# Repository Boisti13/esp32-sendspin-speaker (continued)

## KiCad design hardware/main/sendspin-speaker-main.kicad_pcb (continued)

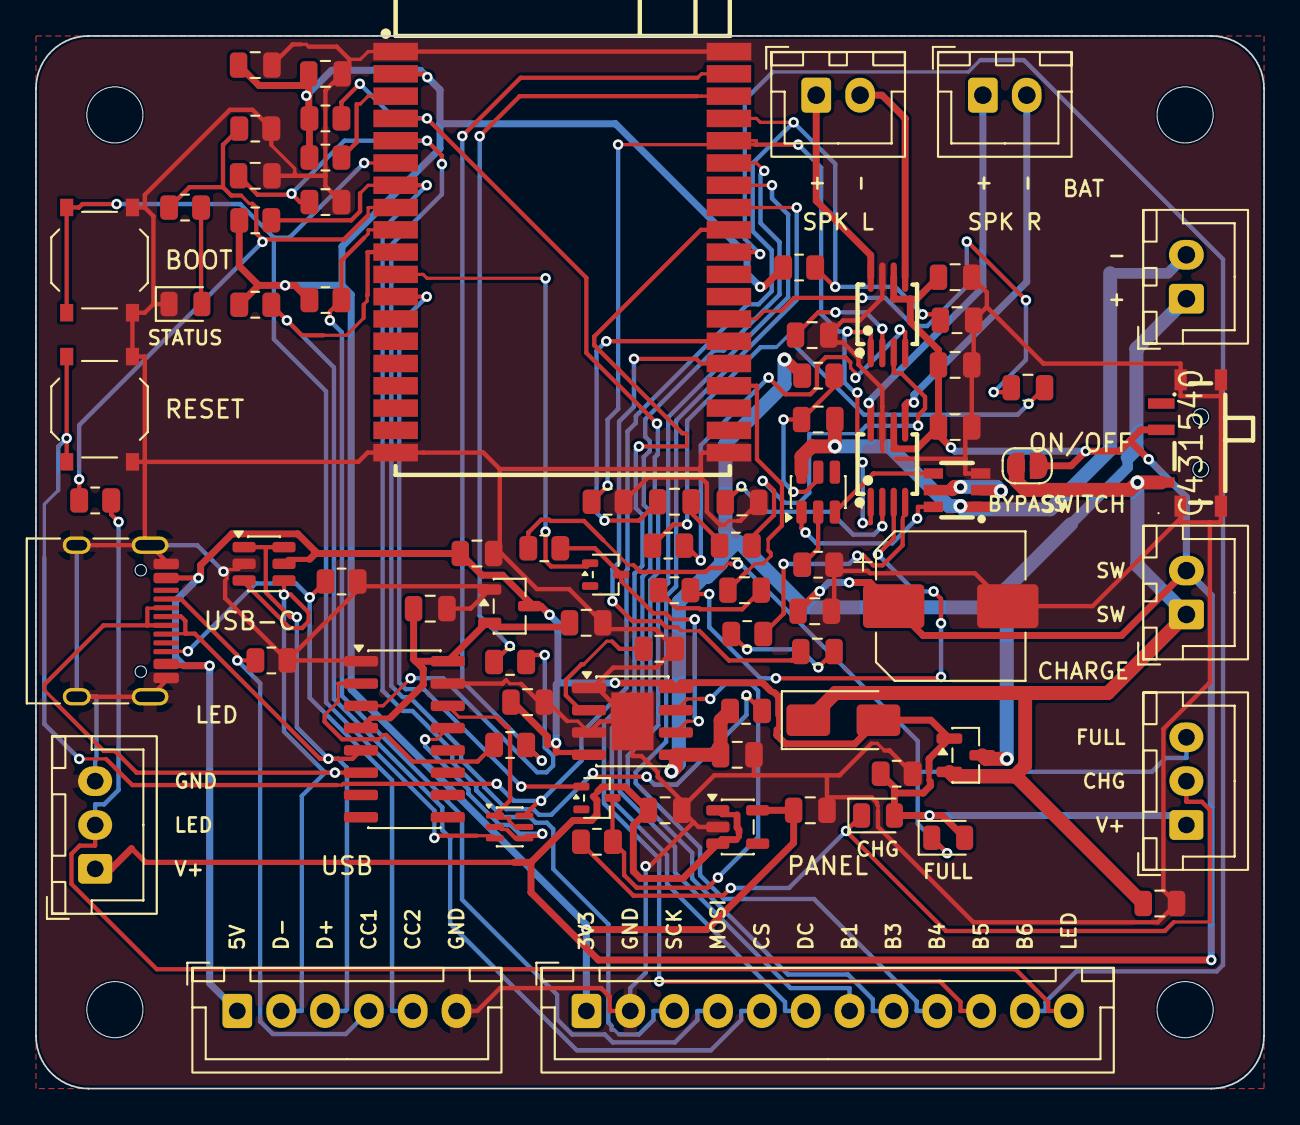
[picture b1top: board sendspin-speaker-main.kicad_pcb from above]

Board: 2 copper layers, 70.0 x 60.0 mm, 85 parts (0 on the bottom side), 65 nets.

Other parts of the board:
H1, H2, H3, H4: MountingHole_3.2mm_M3

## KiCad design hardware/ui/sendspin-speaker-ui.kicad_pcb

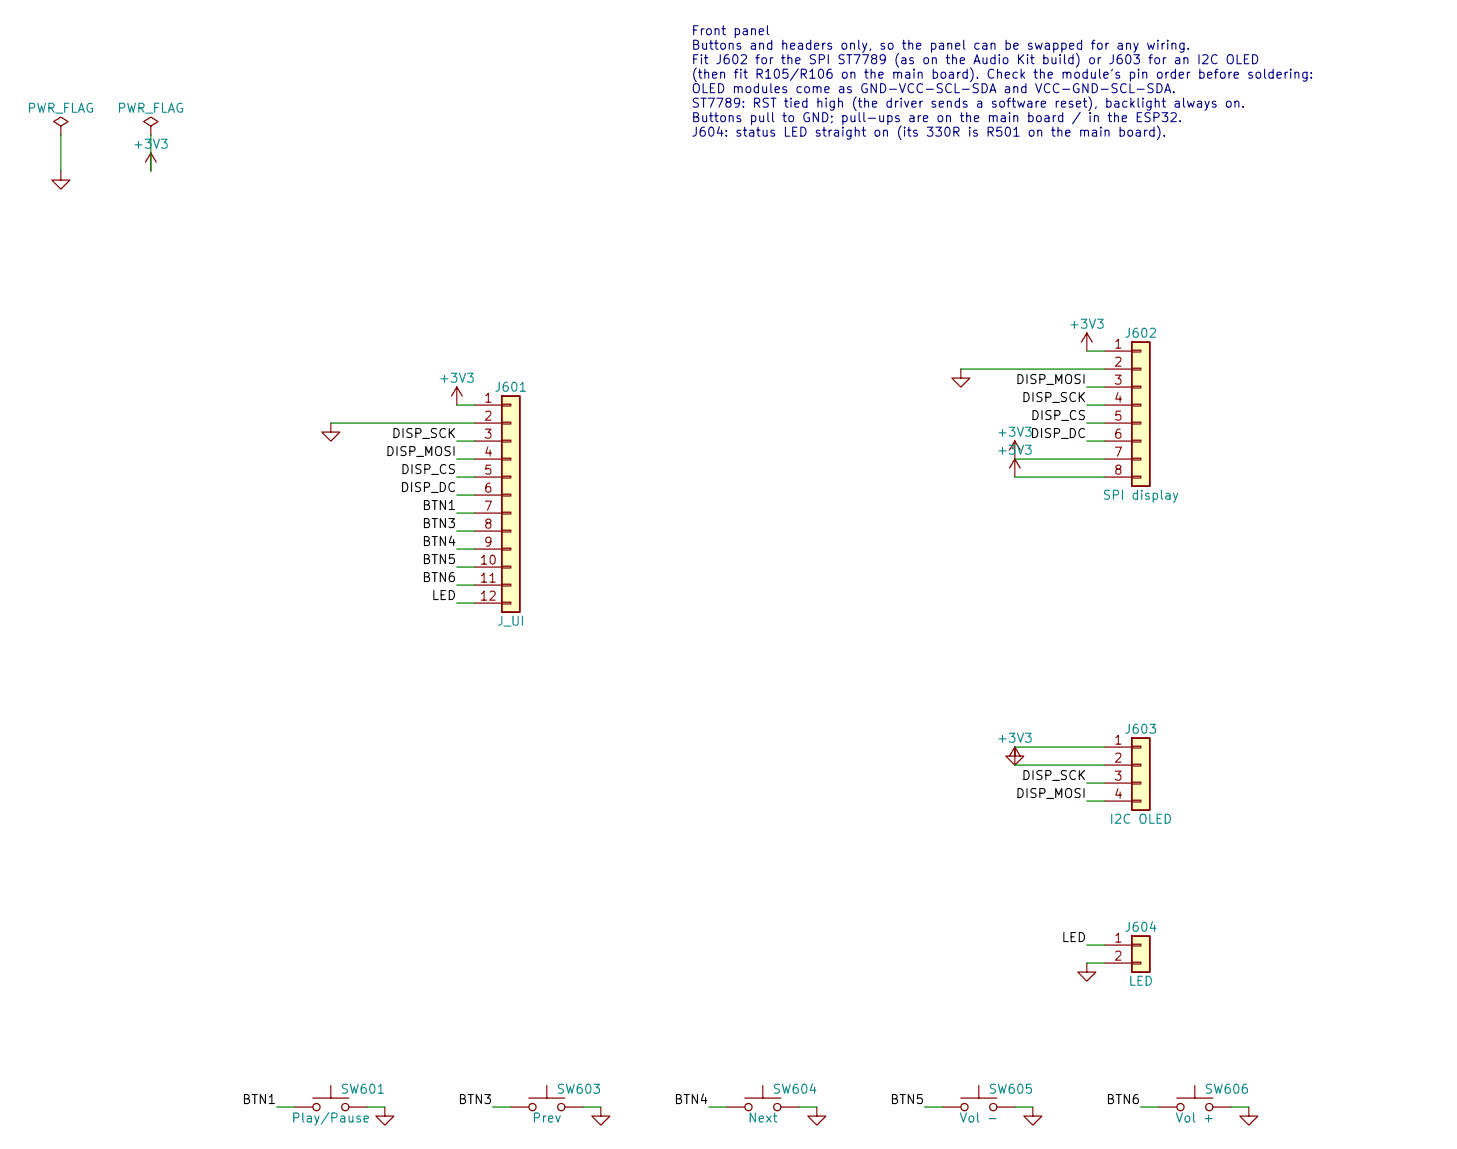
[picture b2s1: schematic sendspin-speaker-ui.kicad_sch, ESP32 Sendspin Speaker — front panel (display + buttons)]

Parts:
J601: J_UI; JST_XH_B12B-XH-A_1x12_P2.50mm_Vertical
J602: SPI display; PinHeader_1x08_P2.54mm_Vertical
J603: I2C OLED; PinHeader_1x04_P2.54mm_Vertical
J604: LED; PinHeader_1x02_P2.54mm_Vertical
SW601: Play/Pause; SW_PUSH_6mm
SW603: Prev; SW_PUSH_6mm
SW604: Next; SW_PUSH_6mm
SW605: Vol -; SW_PUSH_6mm
SW606: Vol +; SW_PUSH_6mm

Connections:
+3V3: J601.1, J602.1, J602.7, J602.8, J603.2
/BTN1: J601.7, SW601.1
/BTN3: J601.8, SW603.1
/BTN4: J601.9, SW604.1
/BTN5: J601.10, SW605.1
/BTN6: J601.11, SW606.1
/DISP_CS: J601.5, J602.5
/DISP_DC: J601.6, J602.6
/DISP_MOSI: J601.4, J602.3, J603.4
/DISP_SCK: J601.3, J602.4, J603.3
/LED: J601.12, J604.1
GND: J601.2, J602.2, J603.1, J604.2, SW601.2, SW603.2, SW604.2, SW605.2, SW606.2

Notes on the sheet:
Front panel Buttons and headers only, so the panel can be swapped for any wiring. Fit J602 for the SPI ST7789 (as on the Audio Kit build) or J603 for an I2C OLED (then fit R105/R106 on the main board). Check the module's pin order before soldering: OLED modules come as GND-VCC-SCL-SDA and VCC-GND-S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

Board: 2 copper layers, 13 parts (1 on the bottom side), 12 nets, no tracks yet.

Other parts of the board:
H1, H2, H3, H4: MountingHole_3.2mm_M3

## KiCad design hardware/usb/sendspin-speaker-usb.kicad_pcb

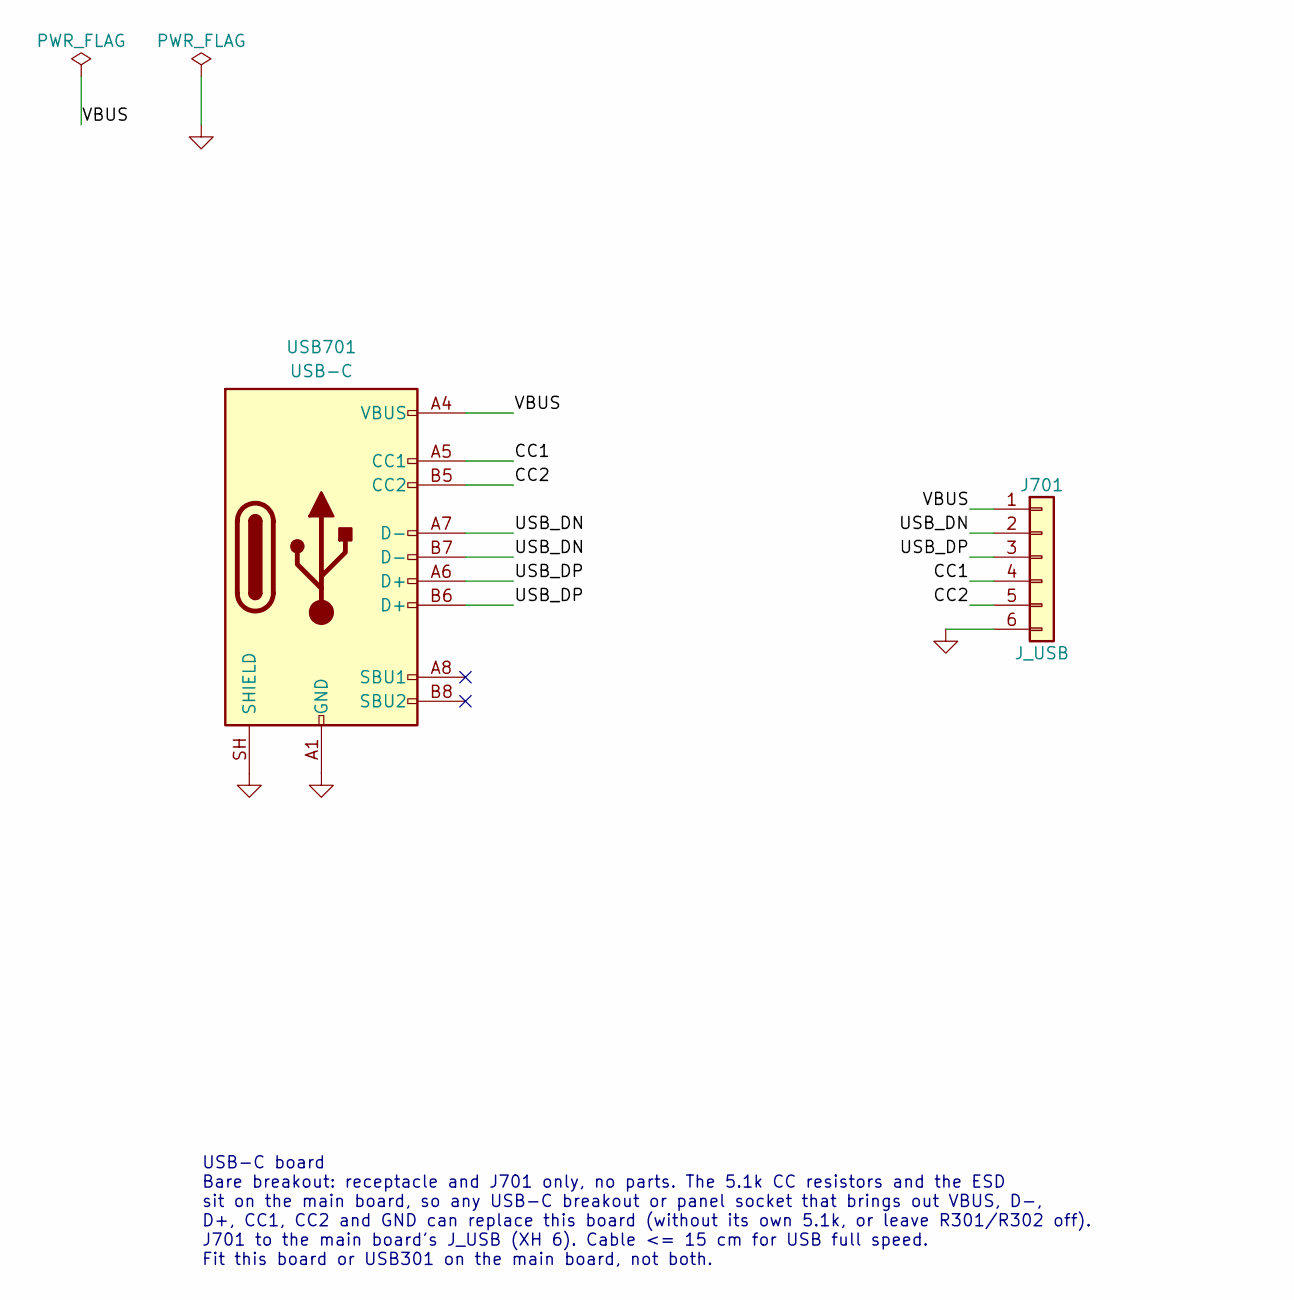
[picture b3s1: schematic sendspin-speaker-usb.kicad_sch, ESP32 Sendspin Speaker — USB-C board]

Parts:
J701: J_USB; JST_XH_B6B-XH-A_1x06_P2.50mm_Vertical
USB701: USB-C; USB_C_Receptacle_HRO_TYPE-C-31-M-12

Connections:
/CC1: J701.4, USB701.A5 (CC1)
/CC2: J701.5, USB701.B5 (CC2)
/USB_DN: J701.2, USB701.A7 (D-), USB701.B7 (D-)
/USB_DP: J701.3, USB701.A6 (D+), USB701.B6 (D+)
/VBUS: J701.1, USB701.A4 (VBUS), USB701.A9 (VBUS), USB701.B4 (VBUS), USB701.B9 (VBUS)
GND: J701.6, USB701.A1 (GND), USB701.A12 (GND), USB701.B1 (GND), USB701.B12 (GND), USB701.SH (SHIELD)

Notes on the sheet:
USB-C board Bare breakout: receptacle and J701 only, no parts. The 5.1k CC resistors and the ESD sit on the main board, so any USB-C breakout or panel socket that brings out VBUS, D-, D+, CC1, CC2 and GND can replace this board (without its own 5.1k, or leave R301/R302 off). J701 to the main board'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

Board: 2 copper layers, 4 parts (0 on the bottom side), 6 nets, no tracks yet.

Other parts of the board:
H1, H2: MountingHole_2.2mm_M2

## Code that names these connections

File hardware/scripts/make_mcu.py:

"""Draw the main board's MCU sheet (mcu.kicad_sch)."""
import sys
sys.path.insert(0, __import__("os").path.dirname(__file__))
from schgen import Sheet

OUT = "D:/dev/esp32-sendspin-speaker/hardware/main/mcu.kicad_sch"
ROOT, SHEET = "1294b3cd-656f-456e-a4e5-c0aee204737d", "314e3d3e-7960-4540-b960-f2a0c4541ea0"
FILE_UUID = "892d340b-2040-41ea-b8fb-889fe8777068"
TITLE = "ESP32 Sendspin Speaker — main board — MCU"

R0805, C0805, LED0805 = ("Resistor_SMD:R_0805_2012Metric", "Capacitor_SMD:C_0805_2012Metric",
                         "LED_SMD:LED_0805_2012Metric")
BUTTON = "Button_Switch_SMD:SW_Push_1P1T_XKB_TS-1187A"

SHAPE = {"U0RXD": "input", "U0TXD": "output", "EN": "input", "IO0": "bidirectional",
         "CHRG": "input", "STDBY": "input", "VBAT_SENSE": "input", "AMP_EN": "output",
         "DISP_SCK": "output", "DISP_MOSI": "bidirectional",
         "DISP_CS": "output", "DISP_DC": "output", "LED": "output"}
for n in ("SPOLP", "SPOLN", "SPORP", "SPORN"):
    SHAPE[n] = "output"
for n in ("BTN1", "BTN3", "BTN4", "BTN5", "BTN6"):
    SHAPE[n] = "input"

# ESP32-A1S pad -> net (None = not connected)
PADS = {1: "GND", 2: "+3V3", 3: "GPIO39", 4: "BTN1", 5: "VBAT_SENSE", 6: "IO0",
        7: "DISP_SCK", 8: "LED", 9: "DISP_MOSI", 10: "DISP_CS", 11: "STDBY", 12: "CHRG",
        13: None, 14: None, 15: None, 16: None, 17: None, 18: None, 19: "GND", 20: "GND",
        21: None, 22: None, 23: "SPORP", 24: "SPORN", 25: "SPOLP", 26: "SPOLN",
        27: None, 28: None, 29: "BTN6", 30: "BTN5", 31: "BTN4", 32: "BTN3",
        33: "DISP_DC", 34: "AMP_EN", 35: "EN", 36: "U0TXD", 37: "U0RXD", 38: "GND"}

s = Sheet("sendspin-speaker-main", f"/{ROOT}/{SHEET}", pwr_base=100)


def hl(pin, net, **kw):
    kind = "hierarchical_label" if net in SHAPE else "label"   # GPIO39: local, spare
    s.attach(pin, net, shape=SHAPE.get(net, "passive"), kind=kind, **kw)


# --- module -----------------------------------------------------------------
u = s.part("lcsc", "ESP32-A1S", "U101", "ESP32-A1S", 80, 100,
           footprint="lcsc:WIRELM-SMD_ESP32-A1S", lcsc="C277945",
           datasheet="https://docs.ai-thinker.com/_media/esp32-a1s_specification.pdf")
for pad, net in PADS.items():
    pin = u[str(pad)]
    if net is None:
        s.no_connect(pin[0], pin[1])
    else:
        # pads 1 and 38 sit next to other pins: longer stubs keep their GND clear of them
        hl(pin, net, stub={1: 10.16, 38: 20.32}.get(pad, 5.08))

# --- supply decoupling (close to pad 2) ---------------------------------------
for i, (ref, val) in enumerate((("C101", "22u"), ("C102", "100n"))):
    c = s.part("Device", "C", ref, val, 150 + 12.7 * i, 45, footprint=C0805)
    hl(c["1"], "+3V3"); hl(c["2"], "GND")

# --- EN: pull-up, RC delay, Reset button ---------------------------------------
r = s.part("Device", "R", "R101", "10k", 190, 45, footprint=R0805)
hl(r["1"], "+3V3"); hl(r["2"], "EN", bend=(5.08, 0))
c = s.part("Device", "C", "C103", "1u", 215, 45, footprint=C0805)
hl(c["1"], "EN", bend=(5.08, 0)); hl(c["2"], "GND")
sw = s.part("Switch", "SW_Push", "SW101", "Reset", 250, 45, footprint=BUTTON)
hl(sw["1"], "EN"); hl(sw["2"], "GND")

# --- pull-ups: input-only GPIO36/39, display CS (strap 15 high), I2C option -----
for i, (ref, val, net, dnp) in enumerate((
        ("R102", "10k", "BTN1", False), ("R103", "10k", "GPIO39", False),
        ("R104", "10k", "DISP_CS", False), ("R105", "4.7k", "DISP_SCK", True),
        ("R106", "4.7k", "DISP_MOSI", True))):
    r = s.part("Device", "R", ref, val, 150 + 22 * i, 90, footprint=R0805, dnp=dnp)
    hl(r["1"], "+3V3"); hl(r["2"], net, bend=(5.08, 0))

# --- Boot button ------------------------------------------------------------
sw = s.part("Switch", "SW_Push", "SW102", "Boot", 160, 135, footprint=BUTTON)
hl(sw["1"], "IO0"); hl(sw["2"], "GND")

# --- status LED on GPIO12 (pull-down keeps the strap low at reset) -------------
r = s.part("Device", "R", "R107", "10k", 195, 135, footprint=R0805)
hl(r["1"], "LED", bend=(5.08, 0)); hl(r["2"], "GND")
r = s.part("Device", "R", "R108", "1k", 220, 135, footprint=R0805)
hl(r["1"], "LED", bend=(5.08, 0))
# LED left of R108: the wire reaches the anode (right pin) without passing the cathode
x, y, _ = r["2"]
d = s.part("Device", "LED", "D101", "green", x - 10.16, y + 7.62, footprint=LED0805)
ax, ay, _ = d["2"]
s.wire(x, y, x, ay); s.wire(x, ay, ax, ay)
hl(d["1"], "GND")

s.text("MCU\n"
       "ESP32-A1S: the codec's I2C (GPIO32/33) and I2S (25/26/27/35, MCLK 0) are inside\n"
       "the module. MIC/LINEIN/HBIAS/MBIAS pads unused.\n"
       "Straps: GPIO12 low at reset (R107), GPIO15 high (R104), GPIO2 low/floating\n"
       "(STDBY via diode on the Power sheet), GPIO0 Boot / auto-reset.\n"
       "R105/R106: fit 4.7k only for an I2C OLED (SCL 14 / SDA 13), leave off for SPI.\n"
       "CHRG (4) / STDBY (2): internal pull-ups in the firmware.\n"
       "C101/C102 next to pad 2 (3V3).", 140, 160)

s.write(OUT, FILE_UUID, TITLE)
print("ok")

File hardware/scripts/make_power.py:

"""Draw the main board's Power sheet (power.kicad_sch)."""
import os, sys
sys.path.insert(0, sys.argv[1] if len(sys.argv) > 1 else os.path.dirname(__file__))
from schgen import Sheet, POWER

OUT = "D:/dev/esp32-sendspin-speaker/hardware/main/power.kicad_sch"
ROOT, SHEET = "1294b3cd-656f-456e-a4e5-c0aee204737d", "7a01c100-f9c5-45b7-af6b-1f2f2d3d81d1"
FILE_UUID = "9ff359a6-4225-41a4-bf38-76fa95de203b"
TITLE = "ESP32 Sendspin Speaker — main board — Power"

R0805, C0805, LED0805 = ("Resistor_SMD:R_0805_2012Metric", "Capacitor_SMD:C_0805_2012Metric",
                         "LED_SMD:LED_0805_2012Metric")
XH = "Connector_JST:JST_XH_B{n}B-XH-A_1x{n:02d}_P2.50mm_Vertical"

HIER = {"VBUS": "input", "CHRG": "output", "STDBY": "output", "VBAT_SENSE": "output"}

s = Sheet("sendspin-speaker-main", f"/{ROOT}/{SHEET}", pwr_base=200)


def net(pin, name, bend=None, stub=2.54):
    """End a pin in a power symbol, hierarchical label or local label, whichever fits."""
    if name in POWER:
        s.attach(pin, name, stub=stub)
    elif name in HIER:
        s.attach(pin, name, stub=stub, shape=HIER[name], bend=bend)
    else:
        s.attach(pin, name, stub=stub, kind="label", bend=bend)


def two(lib, name, ref, value, x, y, top, bottom, fp, **kw):
    """Vertical two-pin part between two nets (labels bend right)."""
    p = s.part(lib, name, ref, value, x, y, footprint=fp, **kw)
    net(p["1"], top, bend=(5.08, 0)); net(p["2"], bottom, bend=(5.08, 0))
    return p


# --- charger -------------------------------------------------------------------
u = s.part("Battery_Management", "TP4056-42-ESOP8", "U201", "TP4056", 80.01, 80.01,
           footprint="Package_SO:SOIC-8-1EP_3.9x4.9mm_P1.27mm_EP2.41x3.3mm",
           datasheet="https://www.lcsc.com/datasheet/C16581.pdf")
net(u["4"], "VBUS", stub=5.08)           # VCC
net(u["8"], "VBUS")                      # CE: always enabled
net(u["1"], "GND", stub=12.7)           # TEMP: no NTC (long stub keeps GND clear of PROG)
net(u["2"], "PROG")
net(u["5"], "VBAT")                      # BAT
net(u["3"], "GND"); s.wire(*u["9"][:2], *u["3"][:2])   # GND, exposed pad tied to it
net(u["7"], "CHRG_N", stub=5.08)
net(u["6"], "STDBY_N", stub=5.08)
two("Device", "R", "R201", "2.4k", 110.49, 80.01, "PROG", "GND", R0805)    # ~500 mA
two("Device", "C", "C201", "10u", 50.8, 55.88, "VBUS", "GND", C0805)
two("Device", "C", "C202", "10u", 125.73, 80.01, "VBAT", "GND", C0805)

# --- charge LEDs (on board or via J_CHG) and GPIO read-back --------------------
for i, (sig, colour, led, res, dio) in enumerate((("CHRG", "red", "D201", "R202", "D203"),
                                                  ("STDBY", "green", "D202", "R203", "D204"))):
    y = 125.73 + 25.4 * i
    d = s.part("Device", "LED", led, colour, 40.64, y, footprint=LED0805)
    net(d["2"], "VBUS"); net(d["1"], f"{sig}_K")
    r = s.part("Device", "R", res, "1k", 76.2, y + 3.81, footprint=R0805)
    net(r["1"], f"{sig}_K", bend=(5.08, 0)); net(r["2"], f"{sig}_N", bend=(5.08, 0))
    b = s.part("Diode", "BAT54W", dio, "BAT54W", 116.84, y,
               footprint="Package_TO_SOT_SMD:SOT-323_SC-70")
    net(b["3"], f"{sig}_N"); net(b["1"], sig); s.no_connect(*b["2"][:2])
j = s.part("Connector_Generic", "Conn_01x03", "J203", "J_CHG", 40.64, 185.42,
           footprint=XH.format(n=3))
net(j["1"], "VBUS"); net(j["2"], "CHRG_K"); net(j["3"], "STDBY_K")

# --- battery and protection (DW01A + FS8205A in the negative lead) -------------
j = s.part("Connector_Generic", "Conn_01x02", "J201", "J_BAT", 180.34, 63.5,
           footprint="Connector_JST:JST_XH_B2B-XH-A_1x02_P2.50mm_Vertical")
net(j["1"], "VBAT"); net(j["2"], "BAT_N")
u = s.part("Battery_Management", "DW01A", "U202", "DW01A", 220.98, 63.5,
           footprint="Package_TO_SOT_SMD:SOT-23-6")
net(u["5"], "DW_VCC"); net(u["6"], "BAT_N"); net(u["2"], "DW_CS")
net(u["1"], "OD", bend=(-5.08, 0)); net(u["3"], "OC", bend=(5.08, 0)); s.no_connect(*u["4"][:2])
two("Device", "R", "R204", "100", 254.0, 50.8, "VBAT", "DW_VCC", R0805)
two("Device", "C", "C203", "100n", 271.78, 50.8, "DW_VCC", "BAT_N", C0805)
two("Device", "R", "R205", "1k", 254.0, 76.2, "DW_CS", "GND", R0805)
q = s.part("lcsc", "FS8205A_C2830320", "Q201", "FS8205A", 220.98, 101.6,
           footprint="lcsc:SOT-23-6_L2.9-W1.6-P0.95-LS2.8-BR", lcsc="C2830320")
net(q["1"], "BAT_N"); net(q["6"], "OD")      # discharge FET on the cell side
net(q["3"], "GND"); net(q["4"], "OC")        # charge FET on the system side
net(q["2"], "FET_D"); net(q["5"], "FET_D")

# --- load sharing: USB feeds the load through SS34, the cell through AO3401A ---
d = s.part("Diode", "SS34", "D205", "SS34", 190.5, 147.32, footprint="Diode_SMD:D_SMA")
net(d["2"], "VBUS"); net(d["1"], "VBAT_LS")
q = s.part("Transistor_FET", "AO3401A", "Q202", "AO3401A", 190.5, 175.26,
           footprint="Package_TO_SOT_SMD:SOT-23")
net(q["1"], "VBUS")                          # gate: off while USB is present
net(q["3"], "VBAT"); net(q["2"], "VBAT_LS", bend=(5.08, 0))  # drain at the cell, source at the load
two("Device", "R", "R206", "100k", 218.44, 160.02, "VBUS", "GND", R0805)
two("Device", "C", "C204", "10u", 236.22, 160.02, "VBAT_LS", "GND", C0805)

# --- on/off: on-board slide switch, panel switch on J_SW, or bridge JP201 ------
sw = s.part("lcsc", "MSK12C02", "SW201", "MSK12C02", 287.02, 154.94,
            footprint="lcsc:SW-TH_MSK12C02", lcsc="C431540",
            texts={"Reference": (12.7, -2.54, "left"), "Value": (0, 8.89, "")})
net(sw["1"], "VBAT_LS", stub=5.08, bend=(-5.08, 0)); net(sw["2"], "VBAT_SW")
s.no_connect(*sw["3"][:2]); net(sw["4"], "GND")   # shell/mounting pads to GND
j = s.part("Connector_Generic", "Conn_01x02", "J202", "J_SW", 287.02, 180.34,
           footprint=XH.format(n=2))
net(j["1"], "VBAT_LS"); net(j["2"], "VBAT_SW", stub=15.24)  # rail symbol clear of pin 1's label
jp = s.part("Jumper", "SolderJumper_2_Open", "JP201", "SW bypass", 287.02, 200.66,
            footprint="Jumper:SolderJumper-2_P1.3mm_Open_RoundedPad1.0x1.5mm", in_bom=False)
net(jp["1"], "VBAT_LS"); net(jp["2"], "VBAT_SW")

# --- 3.3 V -------------------------------------------------------------------------
u = s.part("Regulator_Linear", "AP2112K-3.3", "U203", "AP2112K-3.3", 345.44, 80.01,
           footprint="Package_TO_SOT_SMD:SOT-23-5",
           texts={"Reference": (0, -8.89, ""), "Value": (0, 10.16, "")})
net(u["1"], "VBAT_SW")                     # VIN
vx, vy, _ = u["1"]; ex, ey, _ = u["3"]      # EN tied to VIN
s.wire(ex, ey, vx - 2.54, ey); s.wire(vx - 2.54, ey, vx - 2.54, vy); s.junction(vx - 2.54, vy)
net(u["2"], "GND"); net(u["5"], "+3V3"); s.no_connect(*u["4"][:2])
two("Device", "C", "C205", "10u", 322.58, 99.06, "VBAT_SW", "GND", C0805)
two("Device", "C", "C206", "10u", 370.84, 99.06, "+3V3", "GND", C0805)

# --- battery voltage: divider on the cell (VBAT_SW reads USB's 4.6 V while charging)
two("Device", "R", "R207", "470k", 330.2, 147.32, "VBAT", "VBAT_SENSE", R0805)
two("Device", "R", "R208", "470k", 330.2, 172.72, "VBAT_SENSE", "GND", R0805)
two("Device", "C", "C207", "100n", 355.6, 172.72, "VBAT_SENSE", "GND", C0805)

# --- power flags: nets fed only through passives or from another sheet ---------
for x, n in ((152.4, "BAT_N"), (172.72, "DW_VCC"), (193.04, "VBAT_SW"), (213.36, "GND")):
    y = 27.94
    s.flag(x, y)
    s.wire(x, y, x, y + 5.08)
    if n in POWER:
        s.power(n, x, y + 5.08)
    else:
        s.label("label", n, x, y + 5.08, (1, 0))

s.text("Power\n"
       "TP4056: R201 2.4k = ~500 mA. CE to VBUS, TEMP to GND (no NTC).\n"
       "Charge LEDs: on board (D201 red, D202 green) or off board on J_CHG; R202/R203 serve both.\n"
       "D203/D204 (BAT54W) let GPIO4/GPIO2 see CHRG/STDBY low without VBUS reaching the pins.\n"
       "  Firmware: charging = CHRG low and STDBY high; full = STDBY low and CHRG high; else no USB.\n"
       "Protection in the negative lead: BAT_N = cell minus, GND = P- (system ground).\n"
       "Load sharing: with USB, Q202 is off and the load runs from VBUS through D205;\n"
       "  without USB, Q202 connects the cell. VBAT_LS = load side before the switch.\n"
       "On/off: fit SW201, or a panel switch on J_SW, or bridge JP201. The cell keeps charging when off.\n"
       "Battery sense on the cell (2x 470k, ~4.5 uA): VBAT_SW would read 4.6 V from USB while charging.\n"
       "J_BAT: check the cell's polarity before plugging in.", 25.4, 228.6)

s.write(OUT, FILE_UUID, TITLE, paper="A3")
print("ok")
